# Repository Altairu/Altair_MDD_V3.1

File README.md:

# Altair_MDD_V3.1

Altair_MDD_V3からCANとリセットスイッチ部分を変更しました
CANのICを代えて従来の1 Mbps通信だけでなく、最大8 MbpsまでのCAN FDに対応してる最新のものにしました
MCP2562-E/SN or TJA1051T/3(TJA1441ATでも可) 

## 回路図

## 実態配線図

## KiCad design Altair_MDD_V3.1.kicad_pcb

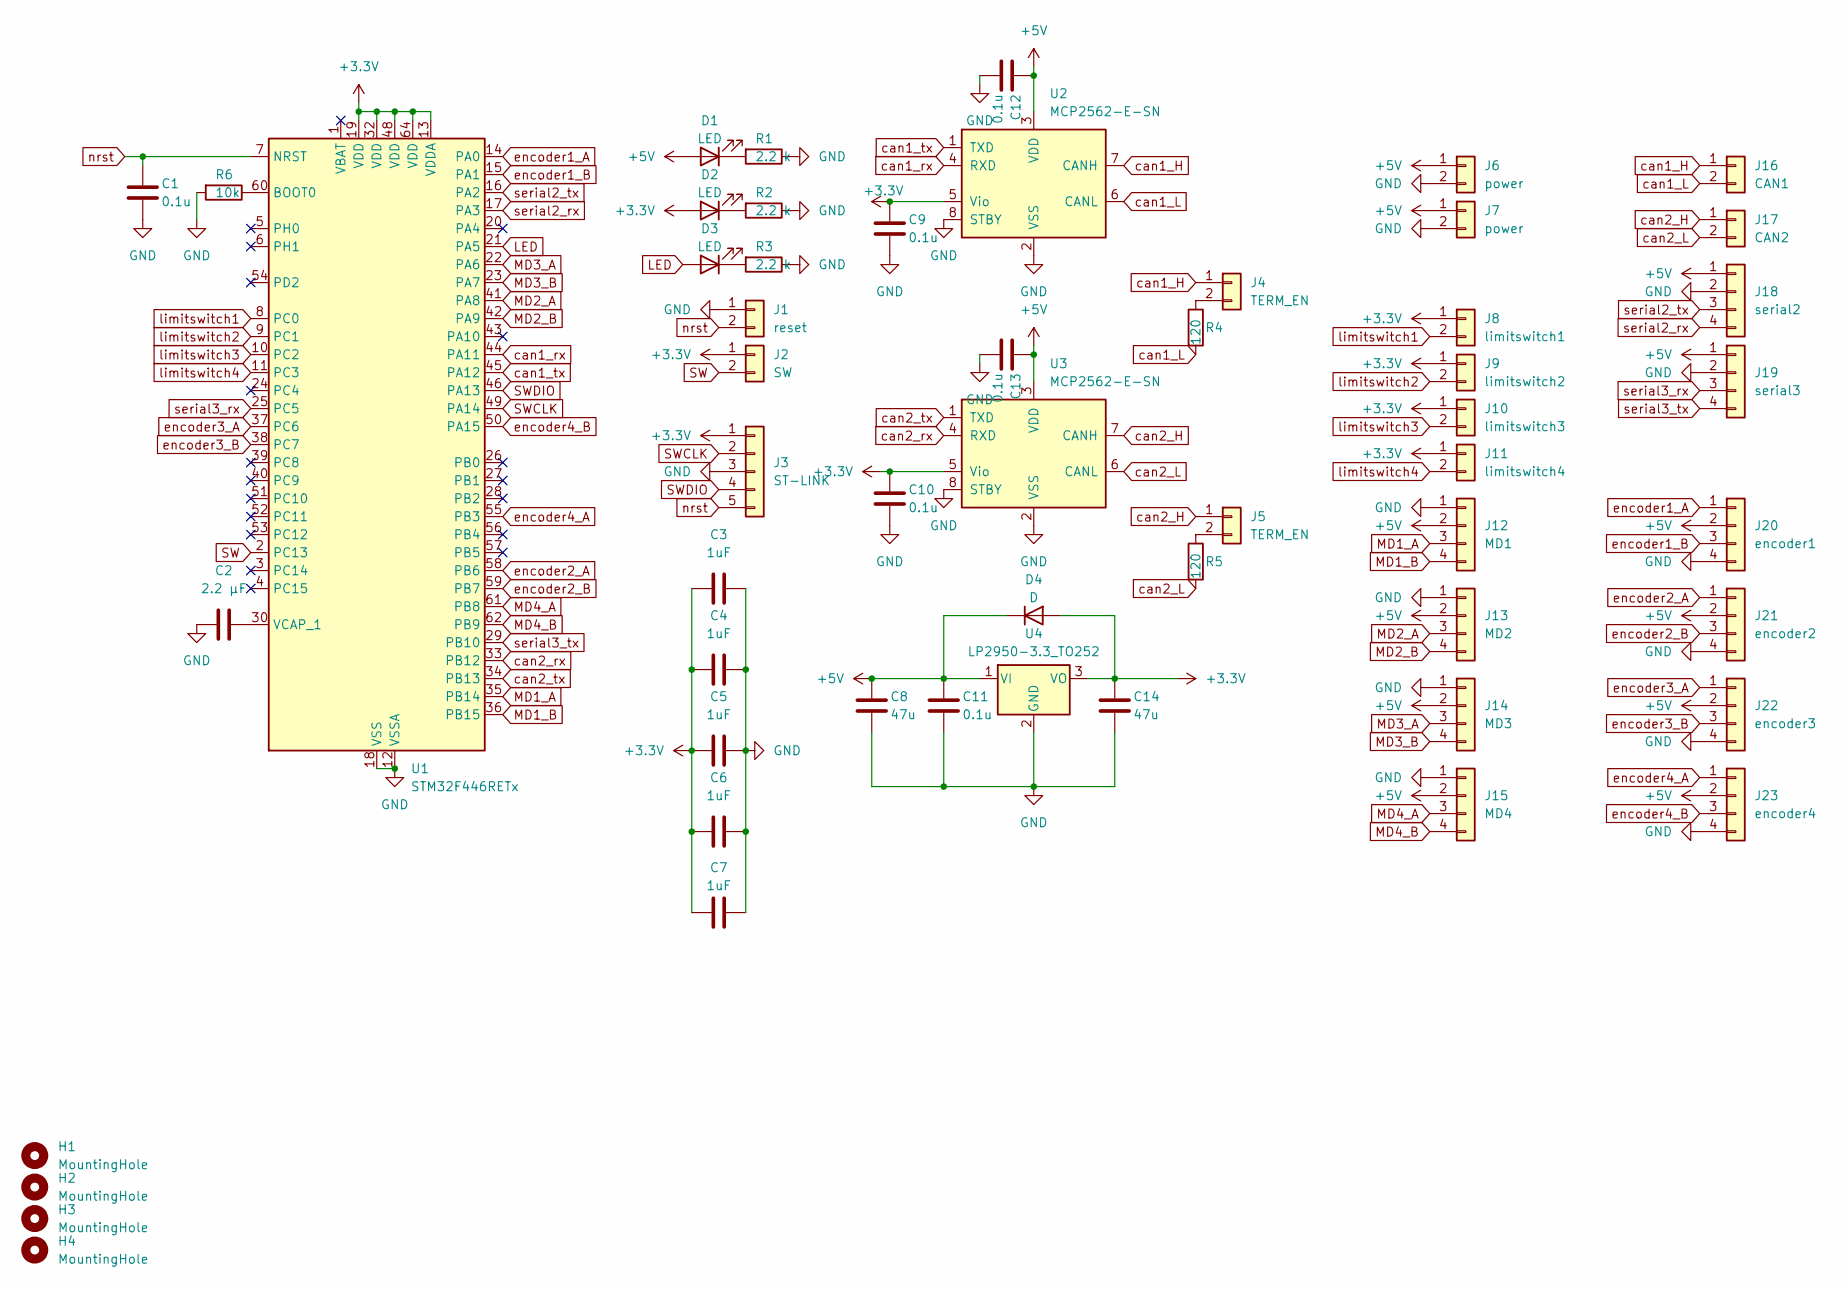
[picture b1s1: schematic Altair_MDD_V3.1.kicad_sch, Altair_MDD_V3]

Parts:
C1, C9, C10, C11, C12, C13: 0.1u; C_0603_1608Metric
C2: 2.2 µF; C_0603_1608Metric
C3, C4, C5, C6, C7: 1uF; C_0603_1608Metric
C8, C14: 47u; C_0603_1608Metric
D1, D2, D3: LED; LED_0603_1608Metric
D4: D; D_0603_1608Metric
H1, H2, H3, H4: MountingHole; MountingHole_3.2mm_M3_Pad_Via
J1: reset; PinSocket_1x02_P2.54mm_Vertical
J2: SW; PinSocket_1x02_P2.54mm_Vertical
J3: ST-LINK; PinSocket_1x05_P2.54mm_Vertical
J4, J5: TERM_EN; PinSocket_1x02_P2.54mm_Vertical
J6, J7: power; JST_XA_S02B-XASK-1_1x02_P2.50mm_Horizontal
J8: limitswitch1; JST_XA_S02B-XASK-1_1x02_P2.50mm_Horizontal
J9: limitswitch2; JST_XA_S02B-XASK-1_1x02_P2.50mm_Horizontal
J10: limitswitch3; JST_XA_S02B-XASK-1_1x02_P2.50mm_Horizontal
J11: limitswitch4; JST_XA_S02B-XASK-1_1x02_P2.50mm_Horizontal
J12: MD1; JST_XA_S04B-XASK-1_1x04_P2.50mm_Horizontal
J13: MD2; JST_XA_S04B-XASK-1_1x04_P2.50mm_Horizontal
J14: MD3; JST_XA_S04B-XASK-1_1x04_P2.50mm_Horizontal
J15: MD4; JST_XA_S04B-XASK-1_1x04_P2.50mm_Horizontal
J16: CAN1; JST_XA_S02B-XASK-1_1x02_P2.50mm_Horizontal
J17: CAN2; JST_XA_S02B-XASK-1_1x02_P2.50mm_Horizontal
J18: serial2; JST_XA_B04B-XASK-1-A_1x04_P2.50mm_Vertical
J19: serial3; JST_XA_B04B-XASK-1-A_1x04_P2.50mm_Vertical
J20: encoder1; JST_XA_S04B-XASK-1_1x04_P2.50mm_Horizontal
J21: encoder2; JST_XA_S04B-XASK-1_1x04_P2.50mm_Horizontal
J22: encoder3; JST_XA_S04B-XASK-1_1x04_P2.50mm_Horizontal
J23: encoder4; JST_XA_S04B-XASK-1_1x04_P2.50mm_Horizontal
R1, R2, R3: 2.2 k; R_0603_1608Metric
R4, R5: 120; R_0603_1608Metric
R6: 10k; R_0603_1608Metric
U1: STM32F446RETx; LQFP-64_10x10mm_P0.5mm
U2, U3: MCP2562-E-SN; SOIC-8_3.9x4.9mm_P1.27mm
U4: LP2950-3.3_TO252; TO-252-2

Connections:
+3.3V: C3.1, C4.1, C5.1, C6.1, C7.1, C9.1, C10.1, C14.1, D2.2 (A), D4.2 (A), J2.1, J3.1, J8.1, J9.1, J10.1, J11.1, U1.13 (VDDA), U1.19 (VDD), U1.32 (VDD), U1.48 (VDD), U1.64 (VDD), U2.5 (Vio), U3.5 (Vio), U4.3 (VO)
+5V: C8.1, C11.1, C12.1, C13.1, D1.2 (A), D4.1 (K), J6.1, J7.1, J12.2, J13.2, J14.2, J15.2, J18.1, J19.1, J20.2, J21.2, J22.2, J23.2, U2.3 (VDD), U3.3 (VDD), U4.1 (VI)
GND: C1.2, C2.1, C3.2, C4.2, C5.2, C6.2, C7.2, C8.2, C9.2, C10.2, C11.2, C12.2, C13.2, C14.2, J1.1, J3.3, J6.2, J7.2, J12.1, J13.1, J14.1, J15.1, J18.2, J19.2, J20.4, J21.4, J22.4, J23.4, R1.1, R2.1, R3.1, R6.2, U1.12 (VSSA), U1.18 (VSS), U1.31 (VSS), U1.47 (VSS), U1.63 (VSS), U2.2 (VSS), U2.8 (STBY), U3.2 (VSS), U3.8 (STBY), U4.2 (GND)
LED: D3.2 (A), U1.21 (PA5)
MD1_A: J12.3, U1.35 (PB14)
MD1_B: J12.4, U1.36 (PB15)
MD2_A: J13.3, U1.41 (PA8)
MD2_B: J13.4, U1.42 (PA9)
MD3_A: J14.3, U1.22 (PA6)
MD3_B: J14.4, U1.23 (PA7)
MD4_A: J15.3, U1.61 (PB8)
MD4_B: J15.4, U1.62 (PB9)
unnamed: D1.1 (K), R1.2
unnamed: D2.1 (K), R2.2
unnamed: D3.1 (K), R3.2
unnamed: J4.2, R4.1
unnamed: J5.2, R5.1
unnamed: R6.1, U1.60 (BOOT0)
unnamed: C2.2, U1.30 (VCAP_1)
SW: J2.2, U1.2 (PC13)
SWCLK: J3.2, U1.49 (PA14)
SWDIO: J3.4, U1.46 (PA13)
can1_H: J4.1, J16.1, U2.7 (CANH)
can1_L: J16.2, R4.2, U2.6 (CANL)
can1_rx: U1.44 (PA11), U2.4 (RXD)
can1_tx: U1.45 (PA12), U2.1 (TXD)
can2_H: J5.1, J17.1, U3.7 (CANH)
can2_L: J17.2, R5.2, U3.6 (CANL)
can2_rx: U1.33 (PB12), U3.4 (RXD)
can2_tx: U1.34 (PB13), U3.1 (TXD)
encoder1_A: J20.1, U1.14 (PA0)
encoder1_B: J20.3, U1.15 (PA1)
encoder2_A: J21.1, U1.58 (PB6)
encoder2_B: J21.3, U1.59 (PB7)
encoder3_A: J22.1, U1.37 (PC6)
encoder3_B: J22.3, U1.38 (PC7)
encoder4_A: J23.1, U1.55 (PB3)
encoder4_B: J23.3, U1.50 (PA15)
limitswitch1: J8.2, U1.8 (PC0)
limitswitch2: J9.2, U1.9 (PC1)
limitswitch3: J10.2, U1.10 (PC2)
limitswitch4: J11.2, U1.11 (PC3)
nrst: C1.1, J1.2, J3.5, U1.7 (NRST)
serial2_rx: J18.4, U1.17 (PA3)
serial2_tx: J18.3, U1.16 (PA2)
serial3_rx: J19.3, U1.25 (PC5)
serial3_tx: J19.4, U1.29 (PB10)

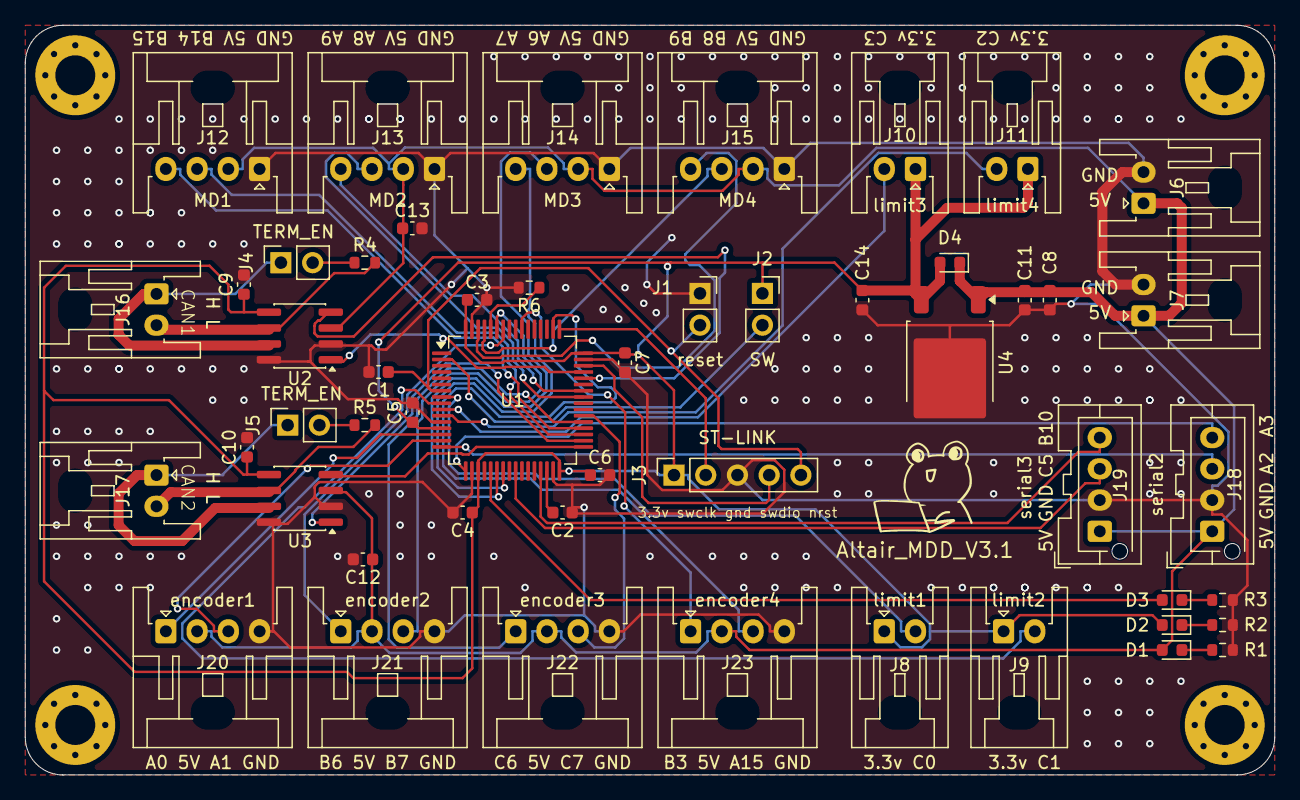
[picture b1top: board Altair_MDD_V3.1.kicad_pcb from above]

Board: 2 copper layers, 100.0 x 60.0 mm, 55 parts (0 on the bottom side), 47 nets.

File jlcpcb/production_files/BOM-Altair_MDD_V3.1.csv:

Comment,Designator,Footprint,LCSC,Quantity
0.1u,"C1,C10,C11,C12,C13,C9",C_0603_1608Metric,C1525,6
10k,R6,R_0603_1608Metric,C25804,1
120,"R4,R5",R_0603_1608Metric,C22787,2
1uF,"C3,C4,C5,C6,C7",C_0603_1608Metric,C1592,5
2.2 k,"R1,R2,R3",R_0603_1608Metric,C4190,3
2.2 µF,C2,C_0603_1608Metric,C23630,1
47u,"C14,C8",C_0603_1608Metric,C140782,2
D,D4,D_0603_1608Metric,C3758192,1
LED,"D1,D2,D3",LED_0603_1608Metric,C2290,3
LP2950-3.3_TO252,U4,TO-252-2,C129994,1
STM32F446RETx,U1,LQFP-64_10x10mm_P0.5mm,C69336,1
MCP2562-E-SN,U3,SOIC-8_3.9x4.9mm_P1.27mm,,1
MCP2562-E-SN,U2,SOIC-8_3.9x4.9mm_P1.27mm,,1
LOGO,G***,LOGO,,1
